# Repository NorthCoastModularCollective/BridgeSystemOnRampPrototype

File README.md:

# BridgeSystemOnRampPrototype
a pure data prototype for the bridge system on ramp

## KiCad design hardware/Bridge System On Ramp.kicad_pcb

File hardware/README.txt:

This folder contains the designs for PCBs, panels, and other hardware items for the Bridge System Onramp.

Pin   Component
0     Decay In
1     MISO (LCD Screen)
2     Trigger button
3     shaper in
4     filter in
5     attack in
6     waveform in
7     DIN (SGTL5000 Audio Chip)
8     DOUT (SGTL5000 Audio Chip)
9     clock Out
10    trigger Out
11    MOSI (LCD Screen)
12    Sequencer Out
13    Sequencer 4th LED
14    LFO Wave
15    Envelope Attack
16    Shaper
17    Filter
18    SDA (SGTL5000 Audio Chip)
19    SCL (SGTL5000 Audio Chip)
20    LRCLCK (SGTL5000 Audio Chip)
21    BLCK (SGTL5000 Audio Chip)
22    LFO Rate
23    LFO Amount
24    Sequencer fader 1
25    Sequencer fader 2
26    Sequencer fader 3
27    Sequencer fader 4
28    LFO Output
29    Sequencer 1st LED
30    Sequencer 2nd LED
31    Sequencer 3rd LED
32    reset (LCD Screen)
33    MCLK (SGTL5000 Audio Chip)
34    Clock Start/stop Button
35    Rotary Encoder A (clock speed)
36    RS (LCD Screen)
37    CS1 (LCD Screen)
38    Rotary Encoder B (clock speed)
39    Clock LED
40    Envelope Decay
41    Oscillator Wave Form

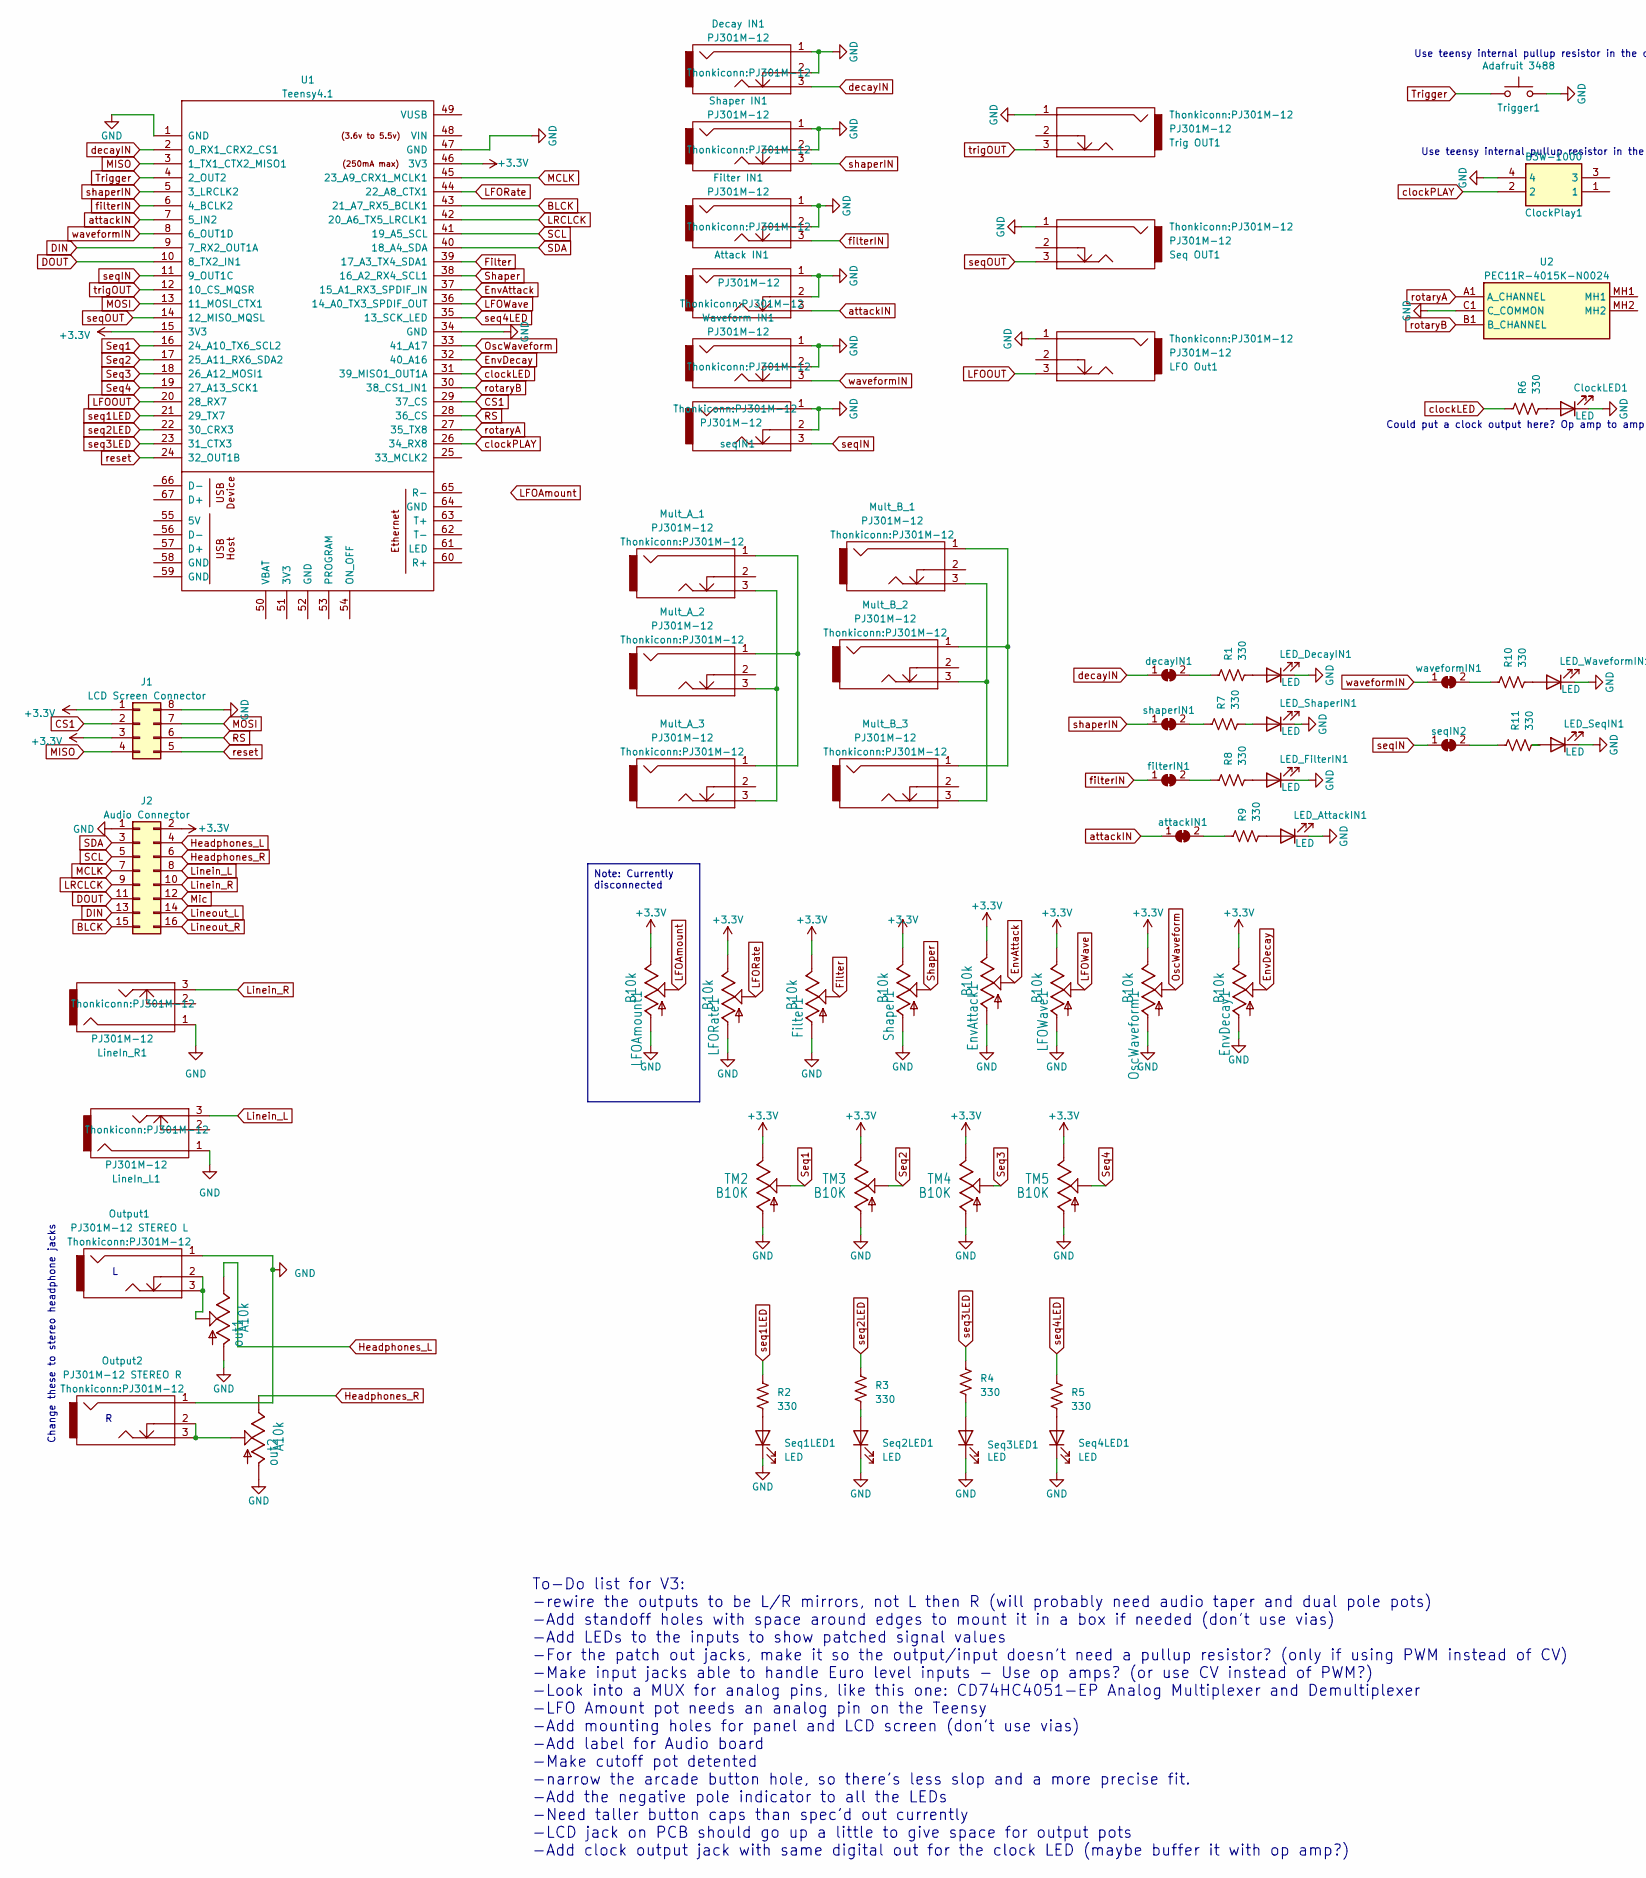
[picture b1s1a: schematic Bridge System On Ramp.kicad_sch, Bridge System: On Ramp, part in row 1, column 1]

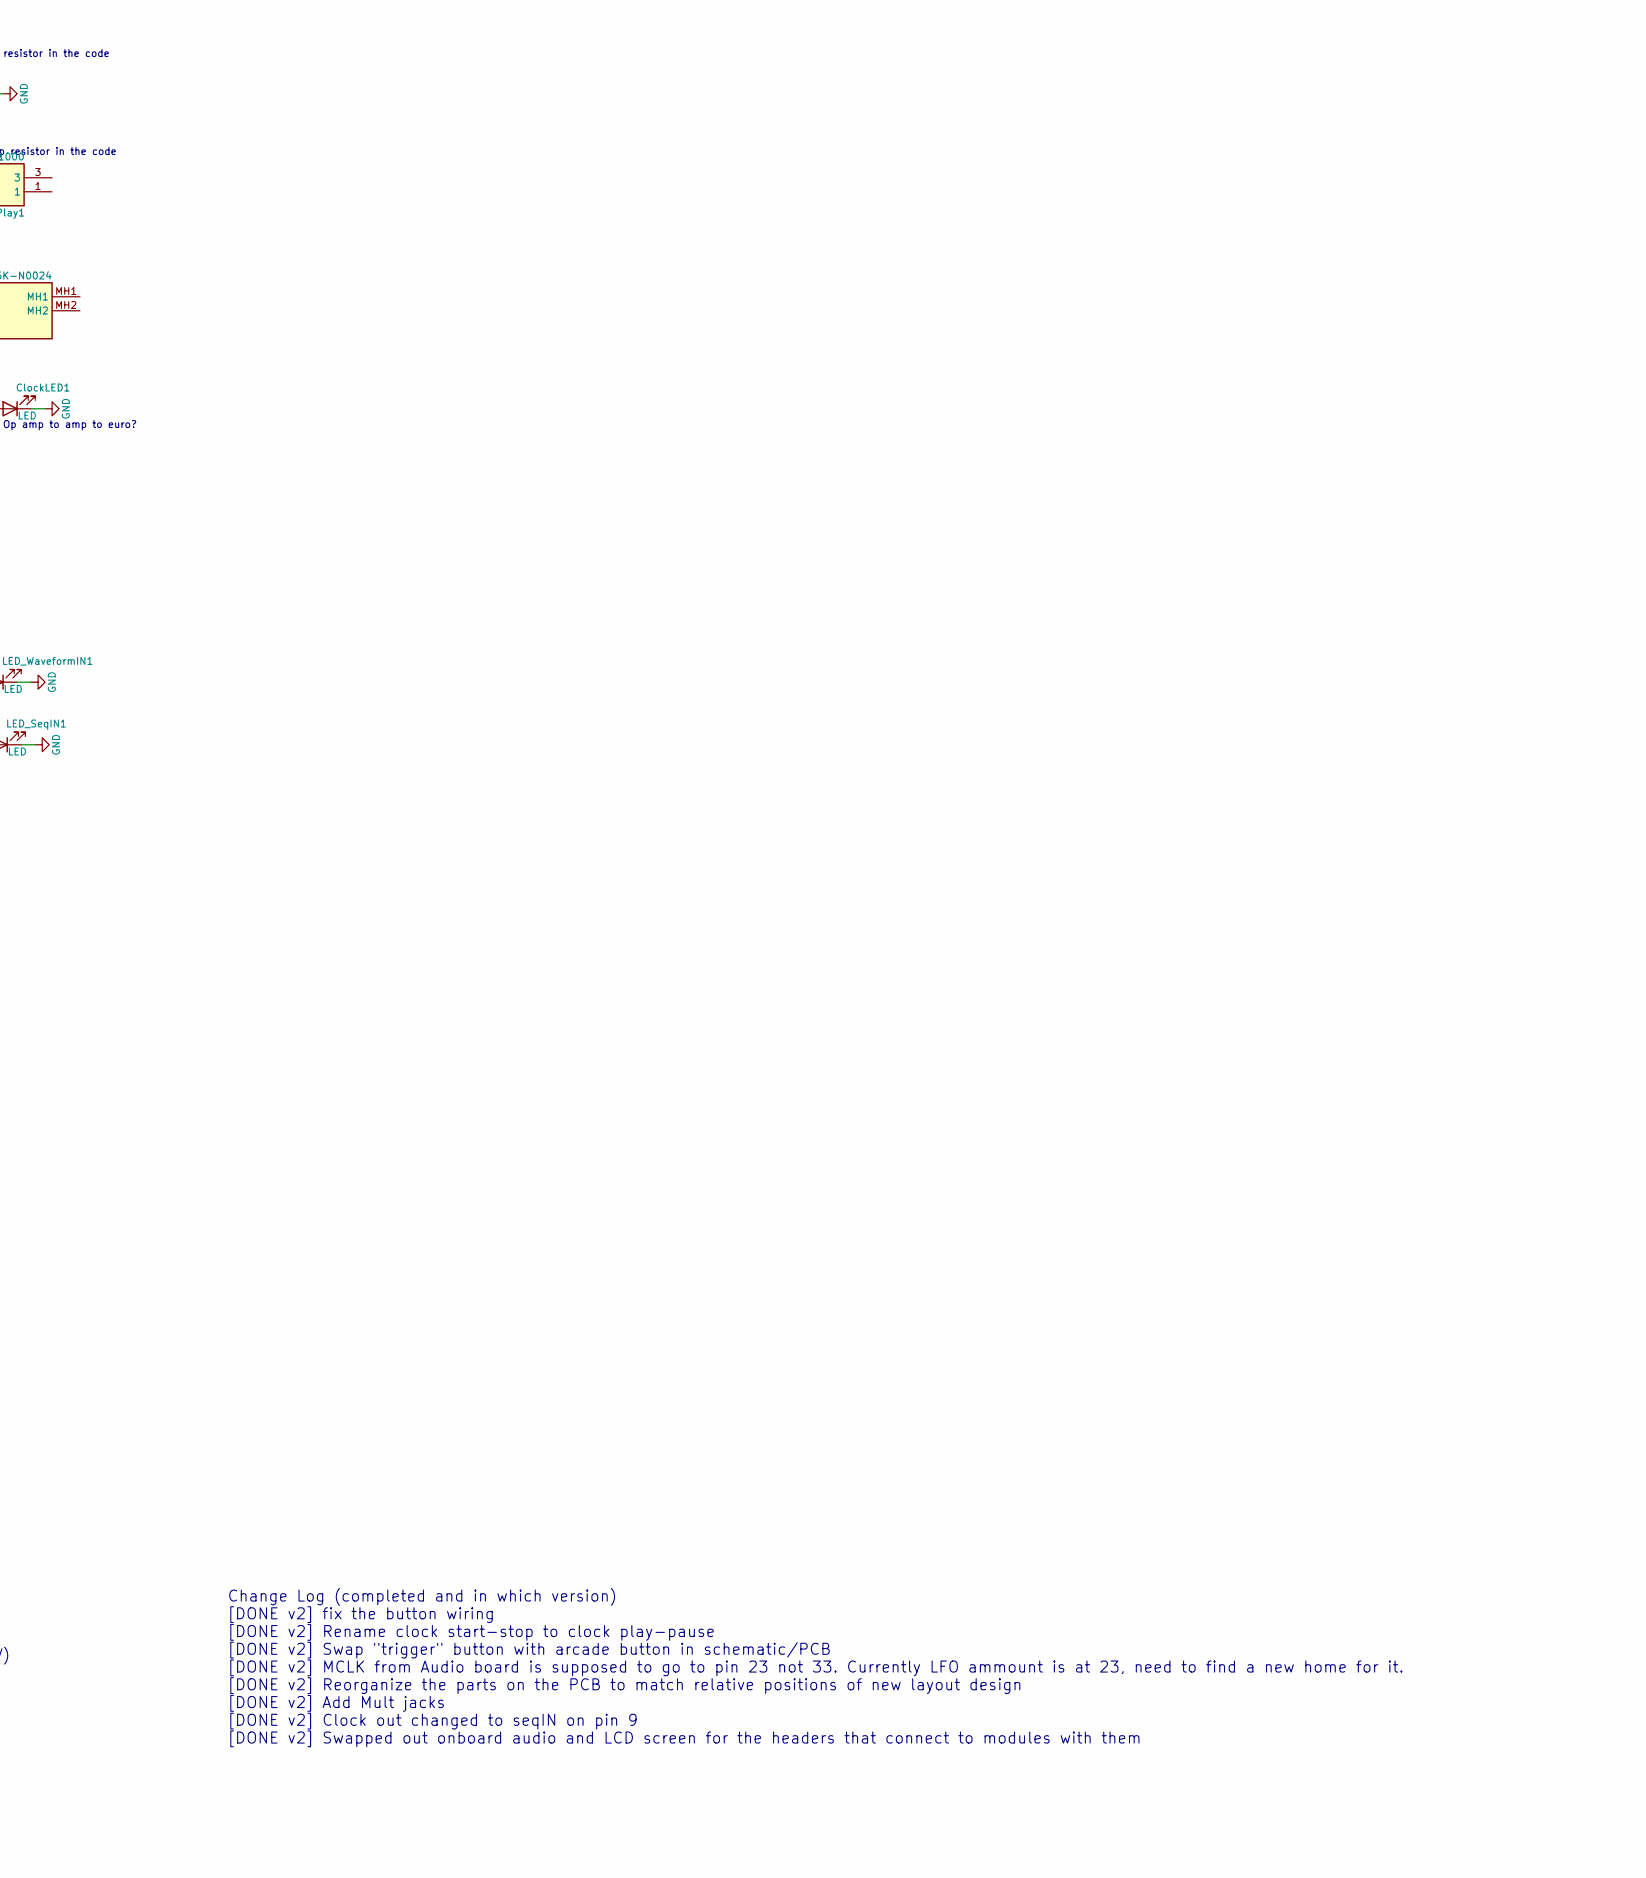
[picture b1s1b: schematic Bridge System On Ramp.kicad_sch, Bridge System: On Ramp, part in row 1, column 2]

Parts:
Attack IN1: PJ301M-12
ClockLED1: LED; LED_D3.0mm
ClockPlay1: B3W-1000; B3W1050; Mouser Part Number 653-B3W-1000
Decay IN1: PJ301M-12
EnvAttack1: B10k; EVUFXL
EnvDecay1: B10k; EVUFXL
Filter1: B10k; EVUFXL
Filter IN1: PJ301M-12
J1: LCD Screen Connector; PinSocket_2x04_P2.00mm_Vertical_SMD
J2: Audio Connector; PinSocket_2x08_P2.00mm_Vertical_SMD; Part Number 1-1602FBV0T
LED_AttackIN1: LED; LED_D3.0mm
LED_DecayIN1: LED; LED_D3.0mm
LED_FilterIN1: LED; LED_D3.0mm
LED_SeqIN1: LED; LED_D3.0mm
LED_ShaperIN1: LED; LED_D3.0mm
LED_WaveformIN1: LED; LED_D3.0mm
LFO Out1: PJ301M-12
LFOAmount1: B10k; EVUFXL
LFORate1: B10k; EVUFXL
LFOWave1: B10k; EVUFXL
LineIn_L1: PJ301M-12
LineIn_R1: PJ301M-12
Mult_A_1, Mult_A_2, Mult_A_3: PJ301M-12
Mult_B_1, Mult_B_2, Mult_B_3: PJ301M-12
OscWaveform1: B10k; EVUFXL
Output1: PJ301M-12 STEREO L; PJ301M-12
Output2: PJ301M-12 STEREO R; PJ301M-12
R1, R2, R3, R4, R5, R6, R7, R8, R9, R10, R11: 330; R_1206_3216Metric_Pad1.30x1.75mm_HandSolder
Seq1LED1, Seq2LED1, Seq3LED1, Seq4LED1: LED; LED_D3.0mm
Seq OUT1: PJ301M-12
Shaper1: B10k; EVUFXL
Shaper IN1: PJ301M-12
TM2, TM3, TM4, TM5: B10K; SLIDEPOT-60
Trig OUT1: PJ301M-12
Trigger1: Adafruit 3488; PinSocket_1x02_P2.54mm_Horizontal; Mouser Part Number 653-B3W-1000
U1: Teensy4.1; Teensy41
U2: PEC11R-4015K-N0024; PEC11R4015KN0024; Mouser Part Number 652-PEC11R-4015K-N24
Waveform IN1: PJ301M-12
attackIN1: (no value)
decayIN1: (no value)
filterIN1: (no value)
out1, out2: A10k; EVUFXL
seqIN1: PJ301M-12
seqIN2: (no value)
shaperIN1: (no value)
waveformIN1: (no value)

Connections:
+3.3V: EnvAttack1.3 (E), EnvDecay1.3 (E), Filter1.3 (E), J1.1, J1.3, J2.2, LFOAmount1.3 (E), LFORate1.3 (E), LFOWave1.3 (E), OscWaveform1.3 (E), Shaper1.3 (E), TM2.B, TM3.B, TM4.B, TM5.B, U1.15 (3V3), U1.46 (3V3)
BLCK: J2.15 (-12V), U1.43 (21_A7_RX5_BCLK1)
CS1: J1.2, U1.29 (37_CS)
DIN: J2.13 (-12), U1.9 (7_RX2_OUT1A)
DOUT: J2.11 (GND), U1.10 (8_TX2_IN1)
EnvAttack: EnvAttack1.2 (S), U1.37 (15_A1_RX3_SPDIF_IN)
EnvDecay: EnvDecay1.2 (S), U1.32 (40_A16)
Filter: Filter1.2 (S), U1.39 (17_A3_TX4_SDA1)
GND: Attack IN1.1, Attack IN1.2, ClockLED1.1 (K), ClockPlay1.4, Decay IN1.1, Decay IN1.2, EnvAttack1.1 (A), EnvDecay1.1 (A), Filter1.1 (A), Filter IN1.1, Filter IN1.2, J1.8, J2.1, LED_AttackIN1.1 (K), LED_DecayIN1.1 (K), LED_FilterIN1.1 (K), LED_SeqIN1.1 (K), LED_ShaperIN1.1 (K), LED_WaveformIN1.1 (K), LFO Out1.1, LFOAmount1.1 (A), LFORate1.1 (A), LFOWave1.1 (A), LineIn_L1.1, LineIn_R1.1, OscWaveform1.1 (A), Output1.1, Output2.1, Seq1LED1.1 (K), Seq2LED1.1 (K), Seq3LED1.1 (K), Seq4LED1.1 (K), Seq OUT1.1, Shaper1.1 (A), Shaper IN1.1, Shaper IN1.2, TM2.A, TM3.A, TM4.A, TM5.A, Trig OUT1.1, Trigger1.2, U1.1 (GND), U1.34 (GND), U1.47 (GND), U2.C1 (C_COMMON), Waveform IN1.1, Waveform IN1.2, out1.1 (A), out2.1 (A), seqIN1.1, seqIN1.2
Headphones_L: J2.4, out1.3 (E)
Headphones_R: J2.6, out2.3 (E)
LFOAmount: LFOAmount1.2 (S)
LFOOUT: LFO Out1.3, U1.20 (28_RX7)
LFORate: LFORate1.2 (S), U1.44 (22_A8_CTX1)
LFOWave: LFOWave1.2 (S), U1.36 (14_A0_TX3_SPDIF_OUT)
LRCLCK: J2.9 (GND), U1.42 (20_A6_TX5_LRCLK1)
Linein_L: J2.8 (+12V), LineIn_L1.3
Linein_R: J2.10 (GND), LineIn_R1.3
Lineout_L: J2.14 (-12V)
Lineout_R: J2.16
MCLK: J2.7 (12V), U1.45 (23_A9_CRX1_MCLK1)
MISO: J1.4, U1.3 (1_TX1_CTX2_MISO1)
MOSI: J1.7, U1.13 (11_MOSI_CTX1)
Mic: J2.12 (GND)
unnamed: ClockLED1.2 (A), R6.1
unnamed: LED_AttackIN1.2 (A), R9.1
unnamed: LED_DecayIN1.2 (A), R1.1
unnamed: LED_FilterIN1.2 (A), R8.1
unnamed: LED_SeqIN1.2 (A), R11.1
unnamed: LED_ShaperIN1.2 (A), R7.1
unnamed: LED_WaveformIN1.2 (A), R10.1
unnamed: Mult_A_1.1, Mult_A_2.1, Mult_A_3.1
unnamed: Mult_A_1.3, Mult_A_2.3, Mult_A_3.3
unnamed: Mult_B_1.1, Mult_B_2.1, Mult_B_3.1
unnamed: Mult_B_1.3, Mult_B_2.3, Mult_B_3.3
unnamed: R2.1, Seq1LED1.2 (A)
unnamed: R3.1, Seq2LED1.2 (A)
unnamed: R4.1, Seq3LED1.2 (A)
unnamed: R5.1, Seq4LED1.2 (A)
unnamed: R9.2, attackIN1.2 (B)
unnamed: R1.2, decayIN1.2 (B)
unnamed: R8.2, filterIN1.2 (B)
unnamed: Output1.2, Output1.3, out1.2 (S)
unnamed: Output2.2, Output2.3, out2.2 (S)
unnamed: R11.2, seqIN2.2 (B)
unnamed: R7.2, shaperIN1.2 (B)
unnamed: R10.2, waveformIN1.2 (B)
OscWaveform: OscWaveform1.2 (S), U1.33 (41_A17)
RS: J1.6, U1.28 (36_CS)
SCL: J2.5 (+12V), U1.41 (19_A5_SCL)
SDA: J2.3, U1.40 (18_A4_SDA)
Seq1: TM2.WIPER, U1.16 (24_A10_TX6_SCL2)
Seq2: TM3.WIPER, U1.17 (25_A11_RX6_SDA2)
Seq3: TM4.WIPER, U1.18 (26_A12_MOSI1)
Seq4: TM5.WIPER, U1.19 (27_A13_SCK1)
Shaper: Shaper1.2 (S), U1.38 (16_A2_RX4_SCL1)
Trigger: Trigger1.1, U1.4 (2_OUT2)
attackIN: Attack IN1.3, U1.7 (5_IN2), attackIN1.1 (A)
clockLED: R6.2, U1.31 (39_MISO1_OUT1A)
clockPLAY: ClockPlay1.2, U1.26 (34_RX8)
decayIN: Decay IN1.3, U1.2 (0_RX1_CRX2_CS1), decayIN1.1 (A)
filterIN: Filter IN1.3, U1.6 (4_BCLK2), filterIN1.1 (A)
reset: J1.5, U1.24 (32_OUT1B)
rotaryA: U1.27 (35_TX8), U2.A1 (A_CHANNEL)
rotaryB: U1.30 (38_CS1_IN1), U2.B1 (B_CHANNEL)
seq1LED: R2.2, U1.21 (29_TX7)
seq2LED: R3.2, U1.22 (30_CRX3)
seq3LED: R4.2, U1.23 (31_CTX3)
seq4LED: R5.2, U1.35 (13_SCK_LED)
seqIN: U1.11 (9_OUT1C), seqIN1.3, seqIN2.1 (A)
seqOUT: Seq OUT1.3, U1.14 (12_MISO_MQSL)
shaperIN: Shaper IN1.3, U1.5 (3_LRCLK2), shaperIN1.1 (A)
trigOUT: Trig OUT1.3, U1.12 (10_CS_MQSR)
waveformIN: U1.8 (6_OUT1D), Waveform IN1.3, waveformIN1.1 (A)

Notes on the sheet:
Note: Currently disconnected
Use teensy internal pullup resistor in the code
Change these to stereo headphone jacks
Could put a clock output here? Op amp to amp to euro?
Change Log (completed and in which version) [DONE v2] fix the button wiring [DONE v2] Rename clock start-stop to clock play-pause [DONE v2] Swap "trigger" button with arcade button in schematic/PCB [DONE v2] MCLK from Audio board is supposed to go to pin 23 not 33. Currently LFO ammount is at 23, n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
To-Do list for V3: -rewire the outputs to be L/R mirrors, not L then R (will probably need audio taper and dual pole pots) -Add standoff holes with space around edges to mount it in a box if needed (don't use vias) -Add LEDs to the inputs to show patched signal values -For the patch out jacks, make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

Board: 2 copper layers, 61 parts (13 on the bottom side), 64 nets, no tracks yet.

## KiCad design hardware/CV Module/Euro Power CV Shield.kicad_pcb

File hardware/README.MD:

This folder contains the designs for PCBs, panels, and other hardware items for the Bridge System Onramp.

Pinout map for v1 hardware
|Pin| MIDI CC | Component|
|----|-----------|----------|
|0| N/A | Decay Input Jack |
|1| N/A | MISO (LCD Screen)|
|2| 17 | Trigger Button|
|3| N/A| SRR (shaper) Input Jack |
|4| N/A | Filter Cutoff Input Jack |
|5| N/A | Envelope Attack Input Jack |
|6| N/A| Waveform Selector Input Jack |
|7| N/A | DIN (SGTL5000 Audio Chip)|
|8| N/A | DOUT (SGTL5000 Audio Chip)|
|9| N/A | Clock Output Jack|
|10| N/A | Trigger Output Jack|
|11| N/A | MOSI (LCD Screen)|
|12| N/A | Sequencer Output Jack|
|13| N/A | Sequencer 4th LED|
|14| 30 | LFO Wave Knob |
|15| 28 | Envelope Attack Input Jack |
|16| 26| SRR (shaper) Input Jack |
|17| 27 | Filter Cutoff Knob |
|18| N/A |SDA (SGTL5000 Audio Chip)|
|19| N/A |SCL (SGTL5000 Audio Chip)|
|20| N/A |LRCLCK (SGTL5000 Audio Chip)|
|21| N/A |BLCK (SGTL5000 Audio Chip)|
|22| 31| LFO Rate Knob |
|23| 32 | LFO Amount Knob |
|24| 44 | Sequencer Fader 1|
|25| 45| Sequencer Fader 2|
|26| 46 | Sequencer Fader 3|
|27| 47 | Sequencer Fader 4|
|28| N/A | LFO Output Jack|
|29| N/A |Sequencer 1st LED|
|30| N/A |Sequencer 2nd LED|
|31| N/A |Sequencer 3rd LED|
|32| N/A | Reset (LCD Screen)|
|33| N/A | MCLK (SGTL5000 Audio Chip)|
|34| 17 | Clock Start/stop Button|
|35| N/A | Rotary Encoder A (clock speed)|
|36| N/A | RS (LCD Screen)|
|37| N/A | CS1 (LCD Screen)|
|38| N/A | Rotary Encoder B (clock speed)|
|39| N/A | Clock LED|
|40| 23 | Envelope Decay Knob|
|41| 25| Oscillator Waveform Knob |

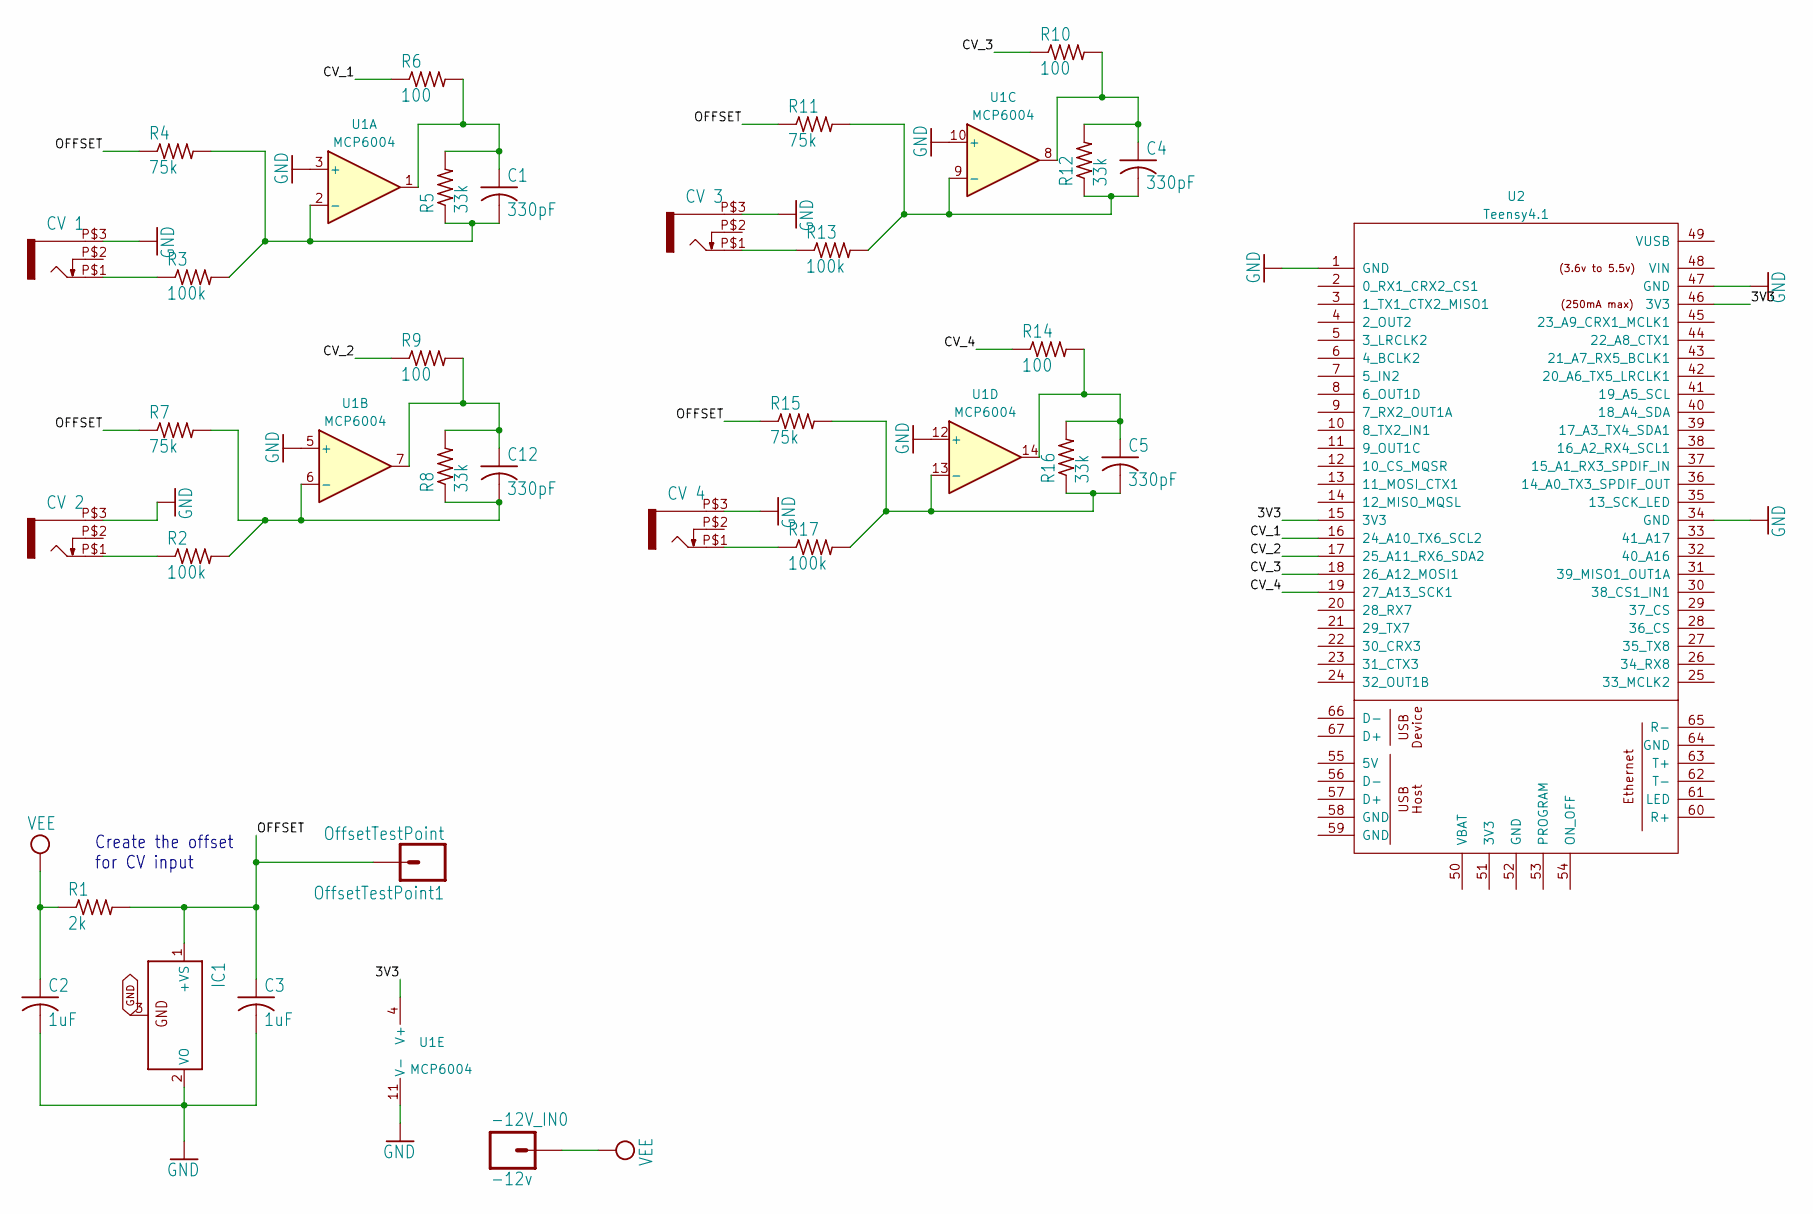
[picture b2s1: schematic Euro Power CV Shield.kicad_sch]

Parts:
-12V_IN0: -12v; 1X01
C1, C4, C5, C12: 330pF; C0805
C2, C3: 1uF; C0805
CV_1: CV 1; WQP-PJ301M-12_JACK
CV_2: CV 2; WQP-PJ301M-12_JACK
CV_3: CV 3; WQP-PJ301M-12_JACK
CV_4: CV 4; WQP-PJ301M-12_JACK
IC1: LM4040DIM3-5.0/NOPB; SOT23
OffsetTestPoint1: OffsetTestPoint; 1X01
R1: 2k; R0805
R2, R3, R13, R17: 100k; R0805
R4, R7, R11, R15: 75k; R0805
R5, R8, R12, R16: 33k; R0805
R6, R9, R10, R14: 100; R0805
U1: MCP6004; DIP-14_W7.62mm
U2: Teensy4.1; Teensy41

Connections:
/3V3: U1.4 (V+), U2.15 (3V3), U2.46 (3V3)
/CV_1: R6.1, U2.16 (24_A10_TX6_SCL2)
/CV_2: R9.1, U2.17 (25_A11_RX6_SDA2)
/CV_3: R10.1, U2.18 (26_A12_MOSI1)
/CV_4: R14.1, U2.19 (27_A13_SCK1)
/OFFSET: C3.1, IC1.1 (+VS), OffsetTestPoint1.1, R1.2, R4.1, R7.1, R11.1, R15.1; also elsewhere on the board
GND: C2.2, C3.2, CV_1.P$3 (1), CV_2.P$3 (1), CV_3.P$3 (1), CV_4.P$3 (1), IC1.2 (VO), IC1.3 (GND), U1.3 (+), U1.5 (+), U1.10 (+), U1.11 (V-), U1.12 (+), U2.1 (GND), U2.34 (GND), U2.47 (GND)
unnamed: C1.1, R5.2, R6.2, U1.1
unnamed: C4.1, R10.2, R12.2, U1.8
unnamed: C5.1, R14.2, R16.2, U1.14
unnamed: C12.1, R8.2, R9.2, U1.7
unnamed: CV_1.P$1 (2), R3.1
unnamed: CV_2.P$1 (2), R2.1
unnamed: CV_3.P$1 (2), R13.1
unnamed: CV_4.P$1 (2), R17.1
unnamed: C1.2, R3.2, R4.2, R5.1, U1.2 (-)
unnamed: C12.2, R2.2, R7.2, R8.1, U1.6 (-)
unnamed: C4.2, R11.2, R12.1, R13.2, U1.9 (-)
unnamed: C5.2, R15.2, R16.1, R17.2, U1.13 (-)
VEE: -12V_IN0.1, C2.1, R1.1; also elsewhere on the board

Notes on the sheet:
Create the offset for CV input

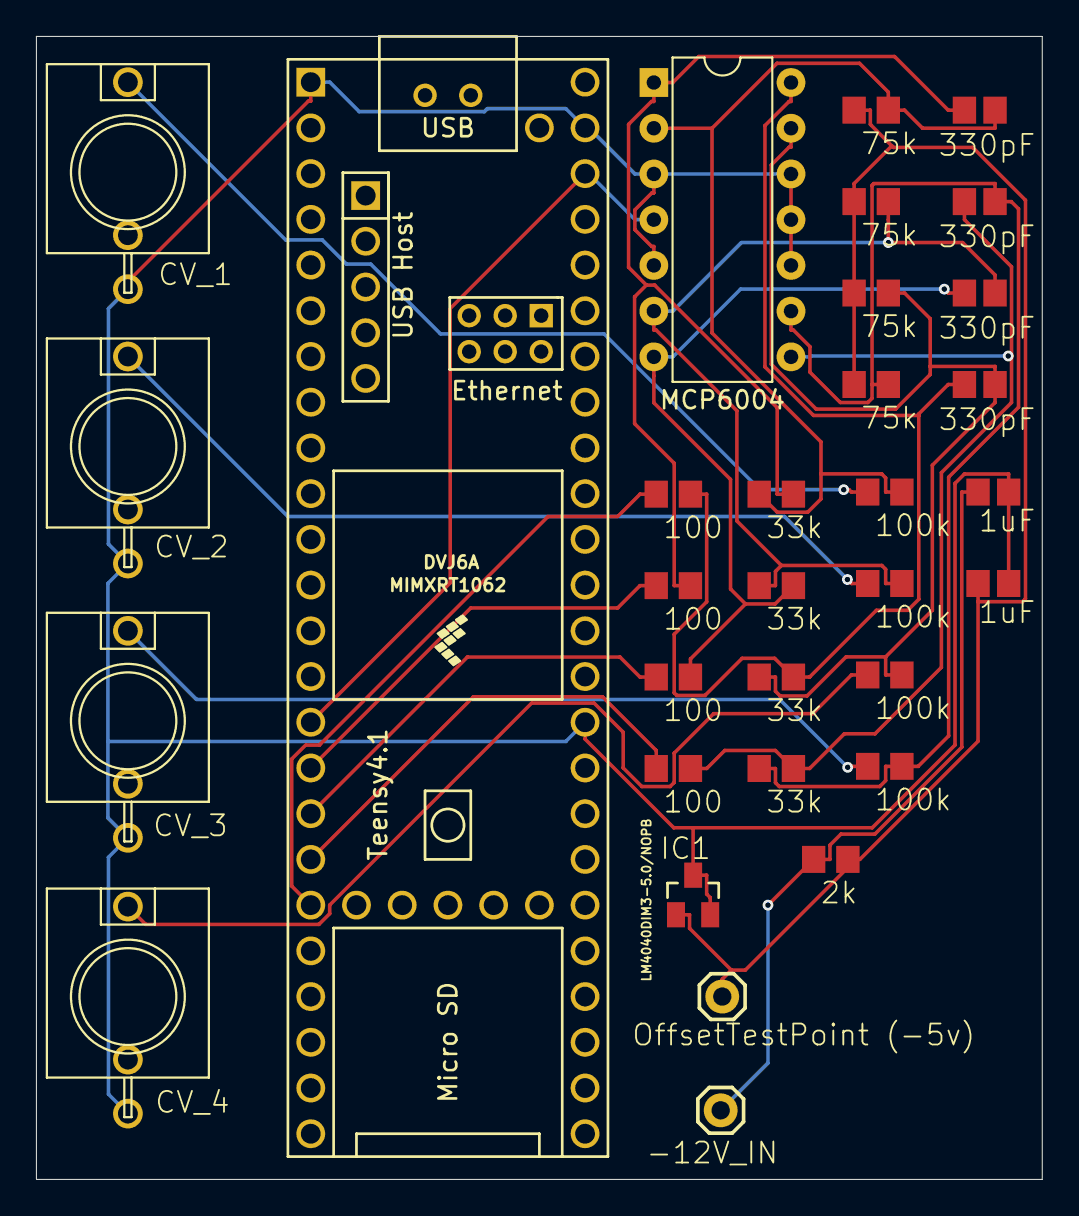
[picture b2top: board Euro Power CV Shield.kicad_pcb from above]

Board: 2 copper layers, 55.9 x 63.5 mm, 32 parts (0 on the bottom side), 20 nets.

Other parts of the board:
-12V_IN: -12v; 1X01
OffsetTestPoint (-5v): OffsetTestPoint; 1X01

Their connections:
/OFFSET: OffsetTestPoint (-5v).1; also elsewhere on the board
VEE: -12V_IN.1; also elsewhere on the board

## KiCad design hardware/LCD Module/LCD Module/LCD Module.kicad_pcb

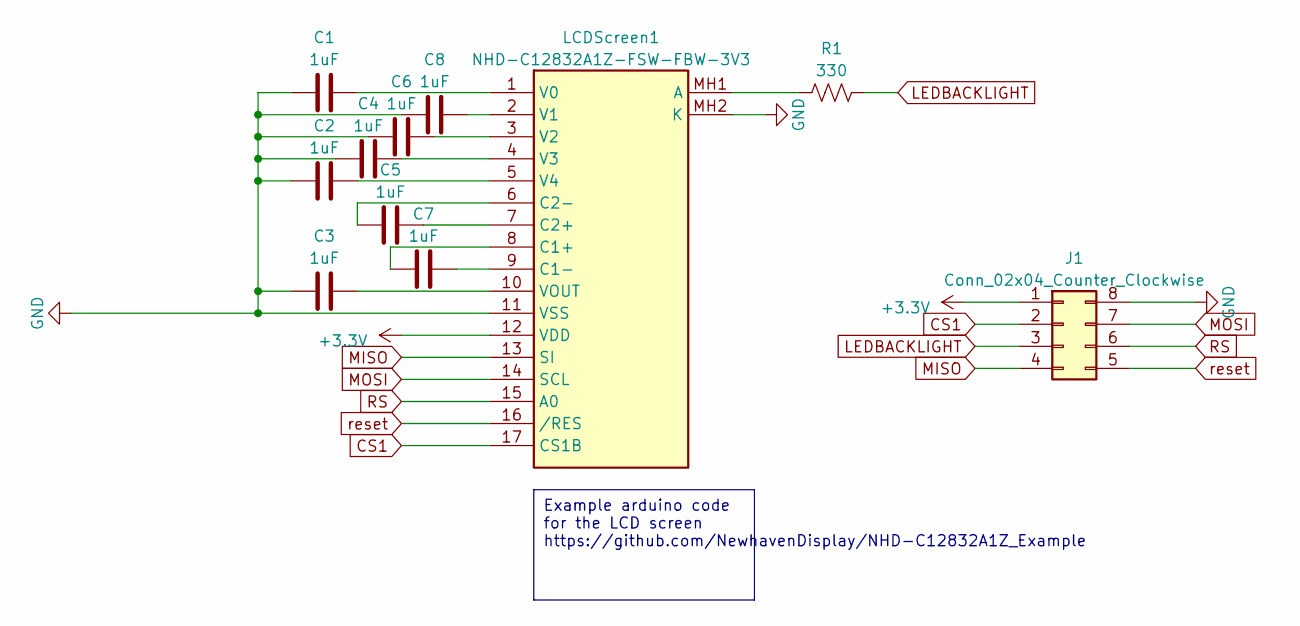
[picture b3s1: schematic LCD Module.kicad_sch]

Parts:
C1, C2, C3, C4, C5, C6, C7, C8: 1uF; C_1206_3216Metric_Pad1.33x1.80mm_HandSolder
J1: Conn_02x04_Counter_Clockwise; PinSocket_2x04_P2.00mm_Vertical_SMD
LCDScreen1: NHD-C12832A1Z-FSW-FBW-3V3; NHDC12832A1ZFSWFBW3V3; Mouser Part Number 763-C12832A1ZFSWFBW3
R1: 330; R_1206_3216Metric

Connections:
+3.3V: J1.1, LCDScreen1.12 (VDD)
CS1: J1.2, LCDScreen1.17 (CS1B)
GND: C1.1, C2.1, C3.1, C4.1, C6.1, C8.1, J1.8, LCDScreen1.11 (VSS), LCDScreen1.MH2 (K)
LEDBACKLIGHT: J1.3, R1.2
MISO: J1.4, LCDScreen1.13 (SI)
MOSI: J1.7, LCDScreen1.14 (SCL)
unnamed: LCDScreen1.MH1 (A), R1.1
unnamed: C7.1, LCDScreen1.8 (C1+)
unnamed: C7.2, LCDScreen1.9 (C1-)
unnamed: C5.2, LCDScreen1.7 (C2+)
unnamed: C5.1, LCDScreen1.6 (C2-)
unnamed: C1.2, LCDScreen1.1 (V0)
unnamed: C8.2, LCDScreen1.2 (V1)
unnamed: C6.2, LCDScreen1.3 (V2)
unnamed: C4.2, LCDScreen1.4 (V3)
unnamed: C2.2, LCDScreen1.5 (V4)
unnamed: C3.2, LCDScreen1.10 (VOUT)
RS: J1.6, LCDScreen1.15 (A0)
reset: J1.5, LCDScreen1.16 (/RES)

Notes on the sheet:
Example arduino code for the LCD screen https://github.com/NewhavenDisplay/NHD-C12832A1Z_Example

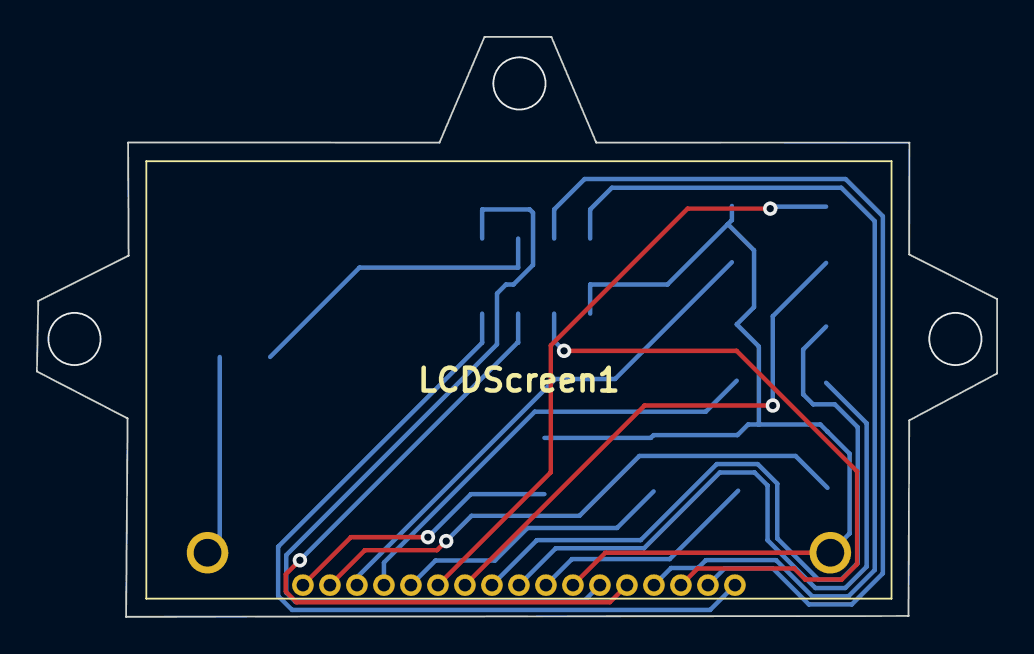
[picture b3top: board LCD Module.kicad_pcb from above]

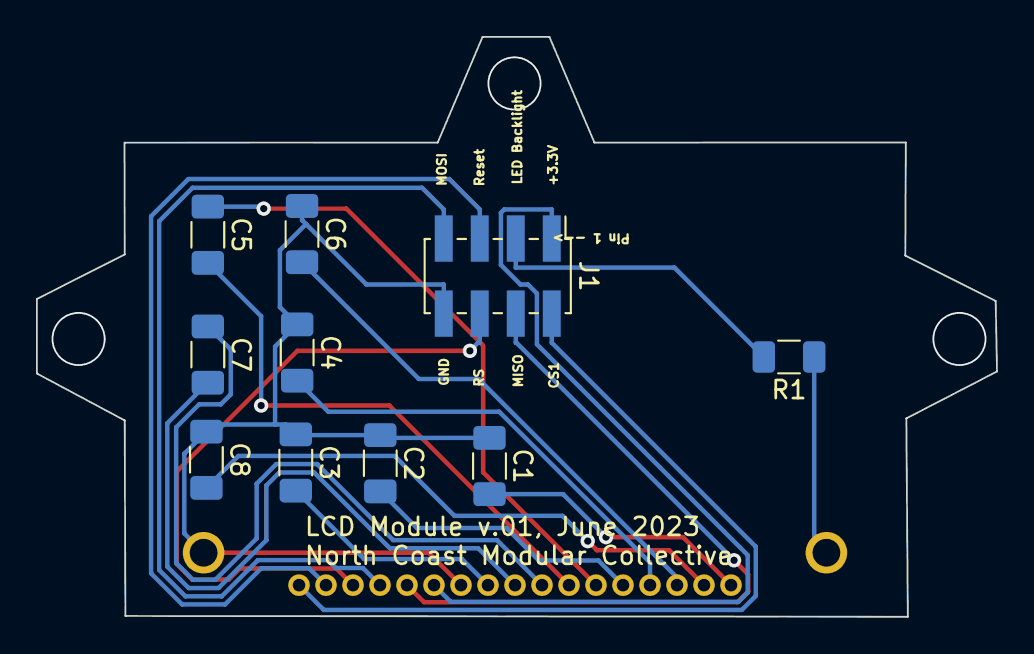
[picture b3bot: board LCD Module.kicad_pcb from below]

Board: 2 copper layers, 53.3 x 32.2 mm, 11 parts (10 on the bottom side), 19 nets.

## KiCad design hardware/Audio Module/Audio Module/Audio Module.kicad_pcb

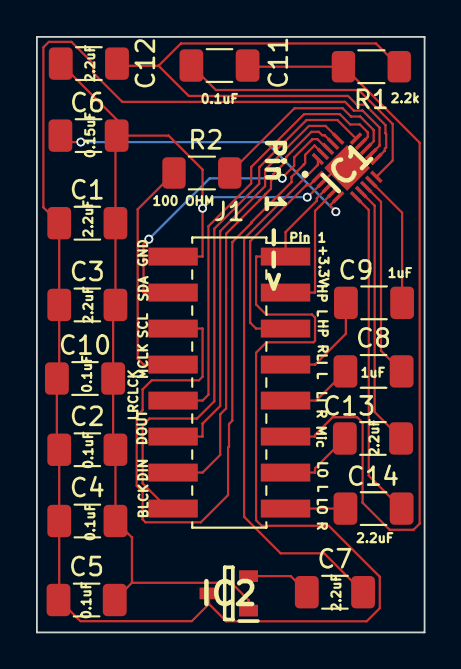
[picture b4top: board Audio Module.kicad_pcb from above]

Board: 2 copper layers, 21.5 x 33.1 mm, 19 parts (0 on the bottom side), 26 nets.

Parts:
C1, C3, C7, C12, C13, C14: 2.2uF; C_1206_3216Metric_Pad1.33x1.80mm_HandSolder
C2, C4, C5, C10, C11: 0.1uF; C_1206_3216Metric_Pad1.33x1.80mm_HandSolder
C6: 0.15uF; C_1206_3216Metric_Pad1.33x1.80mm_HandSolder
C8, C9: 1uF; C_1206_3216Metric_Pad1.33x1.80mm_HandSolder
IC1: SGTL5000XNLA3R2; QFN40P300X300X60-21N
IC2: AP7313-18SRG-7; SOT96P240X135-3N
J1: Conn_02x08; PinSocket_2x08_P2.00mm_Vertical_SMD
R1: 2.2k; R_1206_3216Metric_Pad1.30x1.75mm_HandSolder
R2: 100 OHM; R_1206_3216Metric_Pad1.30x1.75mm_HandSolder

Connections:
+3.3V: C1.1, C2.1, C3.1, C4.1, C5.1, C10.1, IC1.3 (VDDA), IC1.12 (VDDIO), IC2.3 (IN), J1.1
BLCK: IC1.15 (I2S_SCLK), J1.16
DIN: IC1.17 (I2S_DIN), J1.14 (-12V)
DOUT: IC1.16 (I2S_DOUT), J1.12 (GND)
GND: C1.2, C2.2, C3.2, C4.2, C5.2, C6.2, C10.2, C12.2, IC1.2 (HP_VGND), IC1.21 (GND), IC2.1 (GND), J1.2
Headphones_L: IC1.4 (HP_L), J1.3
Headphones_R: IC1.1 (HP_R), J1.5 (+12V)
LRCLCK: IC1.14 (I2S_LRCLK), J1.10 (GND)
Linein_L: C9.2, J1.7 (12V)
Linein_R: C8.1, J1.9 (GND)
Lineout_L: C13.2, J1.13 (-12)
Lineout_R: C14.2, J1.15 (-12V)
MCLK: J1.8 (+12V), R2.2
Mic: C11.2, J1.11 (GND), R1.2
unnamed: C9.1, IC1.9 (LINEIN_L)
unnamed: C8.2, IC1.8 (LINEIN_R)
unnamed: C13.1, IC1.7 (LINEOUT_L)
unnamed: C14.1, IC1.6 (LINEOUT_R)
unnamed: C11.1, IC1.10 (MIC)
unnamed: C12.1, IC1.11 (MIC_BIAS), R1.1
unnamed: IC1.13 (SYS_MCLK), R2.1
unnamed: C6.1, IC1.5 (VAG)
unnamed: C7.2, IC1.20 (VDDD)
unnamed: C7.1, IC2.2 (OUT)
SCL: IC1.19 (CTRL_CLK), J1.6
SDA: IC1.18 (CTRL_DATA), J1.4

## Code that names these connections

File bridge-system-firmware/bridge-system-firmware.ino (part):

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
#define DECAY_IN_PIN 0                 // Decay In
#define MISO_LCD_PIN 1                 // MISO (LCD Screen)
#define TRIGGER_BUTTON_PIN 2           // Trigger button
#define SHAPER_IN_PIN 3                // shaper in
#define FILTER_IN_PIN 4                // filter in
#define ATTACK_IN_PIN 5                // attack in
#define WAVEFORM_IN_PIN 6              // waveform in
#define DIN_AUDIO_PIN 7                // DIN (SGTL5000 Audio Chip)
#define DOUT_AUDIO_PIN 8               // DOUT (SGTL5000 Audio Chip)
#define CLOCK_OUT_PIN 9                // clock Out
#define TRIGGER_OUT_PIN 10             // trigger Out
#define MOSI_LCD_PIN 11                // MOSI (LCD Screen)
#define SEQUENCER_OUT_PIN 12           // Sequencer Out
#define LFO_WAVE_KNOB_PIN 14           // LFO Wave
#define ENV_ATTACK_KNOB_PIN 15         // Envelope Attack
#define SHAPER_KNOB_PIN 16             // Shaper
#define FILTER_KNOB_PIN 17             // Filter
#define SDA_AUDIO_PIN 18               // SDA (SGTL5000 Audio Chip)
#define SCL_AUDIO_PIN 19               // SCL (SGTL5000 Audio Chip)
#define LRCLCK_AUDIO_PIN 20            // LRCLCK (SGTL5000 Audio Chip)
#define BLCK_AUDIO_PIN 21              // BLCK (SGTL5000 Audio Chip)
#define LFO_RATE_KNOB_PIN 22           // LFO Rate
#define LFO_AMOUNT_KNOB_PIN 23         // LFO Amount
#define SEQ_FADER1_PIN 24              // Sequencer fader 1
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#define SEQUENCER_LED3_PIN 31          // Sequencer 3rd LED
#define SEQUENCER_LED4_PIN 13          // Sequencer 4th LED
#define RESET_LCD_PIN 32               // reset (LCD Screen)
#define MCLK_AUDIO_PIN 33              // MCLK (SGTL5000 Audio Chip)
#define CLOCK_START_STOP_BUTTON_PIN 34 // Clock Start/stop Button
#define CLOCK_SPEED_ENCODER_PINA 35    // Rotary Encoder A (clock speed)
#define RS_LCD_PIN 36                  // RS (LCD Screen)
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
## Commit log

2022-07-23 adding current state of prototype
2022-07-23 Bugfix summary
    Bug fixes:
    1. Refactored downsampling-filter logic from Saw-Square core into abstraction and added to SRR output to prevent clicking.
    2. Clipped modulation for Attack and Decay parameters to usable range
    3. Changed minimum Decay value to 5ms
    4. Fixed Speed control knob on Wave submodule
2022-07-23 fixed default value for filter object
2022-07-23 added sane default values and fixed scaling on midi knob
2022-07-24 made a sequencer!
2022-07-24 can now play keyboard... added some color
2022-07-24 experimented with adding some rough symbols and signal flow
2022-08-04 Create \hardware
2022-08-04 Create hardware
2022-08-04 Create Bridge System Onramp interface ideas v2.pdf
    First check-in of the front panel layout. This is a very rough start at laying out the panel for the Bridge System Onramp synth.
2023-05-18 version 1
    Warning: These files are under active development and have not yet been tested.
2023-05-24 v1 BOM added
2023-06-09 Update README.txt
    added Teensy pin mappings
2023-06-09 first pass at hello world sketch
    All four LEDs on
2023-06-09 added a sketch with pin assignments and usb midi prototype
2023-06-09 whoops... used led pins instead of fader pins... fader 4 mysteriously worked?
2023-06-09 added the other knobs to midi out
2023-06-09 fixed cc knobs
2023-06-09 updated CCs on sequencer Pd patch
2023-06-16 First panel design for prototype
    First panel design for prototype, created in Fusion 360
2023-06-16 Create README.MD
    Moved README.txt to README.MD to enable Github tables
2023-06-16 Renamed README.TXT to README.MD
    Renamed README.TXT to README.MD to enable Github table formatting
2023-06-16 added buttons to pd patch
2023-06-16 firmware sends button presses?
2023-06-16 Update README.MD
    Updated table with corresponding CC values
2023-06-16 Update README.MD
    Formatting tweaks
2023-06-16 adding gitignore
2023-06-16 Update README.MD
    Updated formatting to distinguish between knobs, jacks, etc
2023-06-16 adding pullup mode for buttons
2023-06-16 Update README.MD
    Updated formatting
2023-06-16 adding spike to turn on led on button press
2023-06-16 who needs semicolons?
2023-06-17 do we have buttons now?
2023-06-17 led test 2
2023-06-27 Update .gitignore
    Updated to try and ignore all .DS_Store files
2023-06-30 New panel layout ideation
2023-10-28 commiting merged changes... may not be functional
2023-10-28 it goes boop
2023-10-28 passthrough and boop to i2s2 output and usb output
2023-11-12 Minor schematic updates - mostly notes to self
2023-11-12 Starting to work on Rev 2 of the HW
2023-11-12 Added an audio module and a LCD module
2023-11-13 Working on v2 of HW
2023-11-28 mostly hardware updates - also MUX chip test code
2023-12-03 V5 to V6 of interface ideas, added V2.0
2023-12-06 updates to schematic

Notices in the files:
bridge-system-firmware/bridge-system-firmware.ino:
Copyright 2023 North Coast Modular Collective
MIT License:
Permission is hereby granted, free of charge, to any person obtaining a copy
